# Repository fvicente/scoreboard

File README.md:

# scoreboard
Bluetooth controlled Scoreboard on VGA

http://www.alfersoft.com.ar/blog/2011/08/30/scoreboard-part-1-vga-signal-from-an-attiny45/
http://www.alfersoft.com.ar/blog/2012/01/23/scoreboard-part-2-reading-uart-from-the-bluetooth-module/
http://www.alfersoft.com.ar/blog/2012/02/01/scoreboard-part-3-final-communicating-with-android-and-more/

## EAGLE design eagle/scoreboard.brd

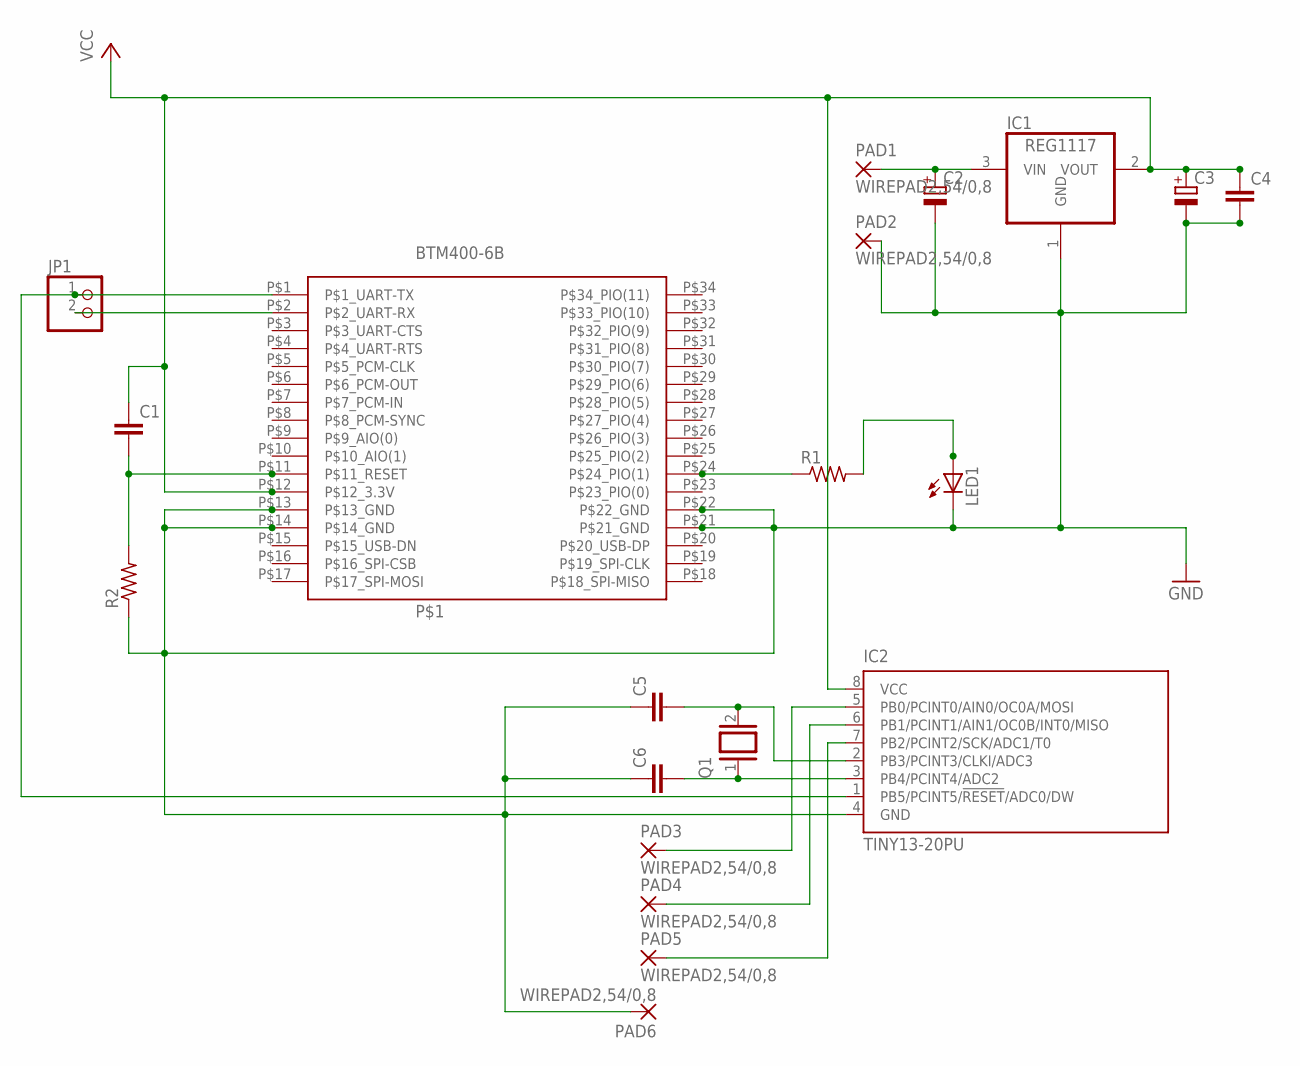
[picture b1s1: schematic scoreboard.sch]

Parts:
C1, C4, C5, C6: C-EU025-025X050; C025-025X050
C2, C3: CPOL-EUE2.5-5; E2,5-5
IC1: REG1117; SOT223
IC2: TINY13-20PU; DIL08
JP1: PINHD-1X2; 1X02
LED1: LED5MM
P$1: BTM400-6B; BTM400
PAD1, PAD2, PAD3, PAD4, PAD5, PAD6: WIREPAD2,54/0,8; 2,54/0,8
Q1: XTAL/S; QS
R1, R2: R-US_0207/10; 0207/10

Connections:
GND: C2.-, C3.-, C4.2, C5.1, C6.1, IC1.1 (GND), IC2.4 (GND), LED1.K (C), P$1.P$13 (P$13_GND), P$1.P$14 (P$14_GND), P$1.P$21 (P$21_GND), P$1.P$22 (P$22_GND), PAD2.1, PAD6.1, R2.1
unnamed: IC2.1 (PB5/PCINT5/!RESET!/ADC0/DW), JP1.1, P$1.P$1 (P$1_UART-TX)
unnamed: P$1.P$24 (P$24_PIO(1)), R1.1
unnamed: LED1.A, R1.2
unnamed: C1.2, P$1.P$11 (P$11_RESET), R2.2
unnamed: JP1.2, P$1.P$2 (P$2_UART-RX)
unnamed: C2.+, IC1.3 (VIN), PAD1.1
unnamed: C6.2, IC2.3 (PB4/PCINT4/ADC2), Q1.1
unnamed: C5.2, IC2.2 (PB3/PCINT3/CLKI/ADC3), Q1.2
unnamed: IC2.5 (PB0/PCINT0/AIN0/OC0A/MOSI), PAD3.1
unnamed: IC2.6 (PB1/PCINT1/AIN1/OC0B/INT0/MISO), PAD4.1
unnamed: IC2.7 (PB2/PCINT2/SCK/ADC1/T0), PAD5.1
VCC: C1.1, C3.+, C4.1, IC1.2 (VOUT), IC2.8 (VCC), P$1.P$12 (P$12_3.3V)

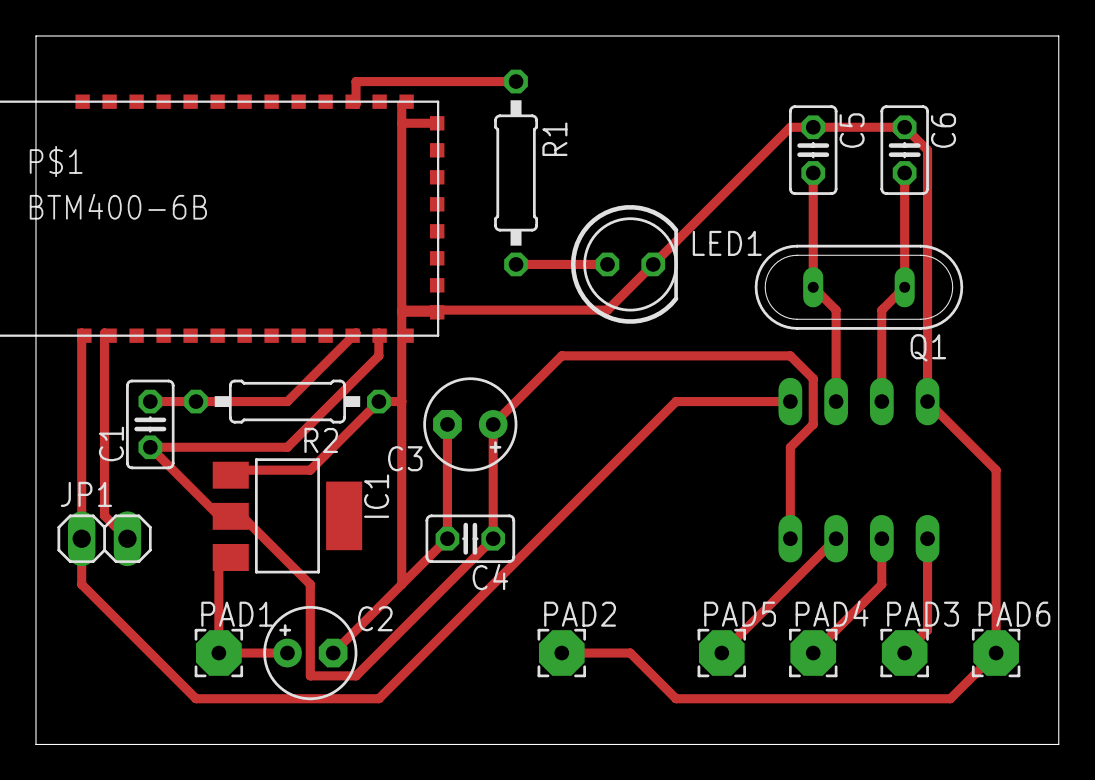
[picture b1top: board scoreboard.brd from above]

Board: 1 copper layer, 56.8 x 39.4 mm, 20 parts (1 on the bottom side), 13 nets.

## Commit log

2016-02-23 Final version
